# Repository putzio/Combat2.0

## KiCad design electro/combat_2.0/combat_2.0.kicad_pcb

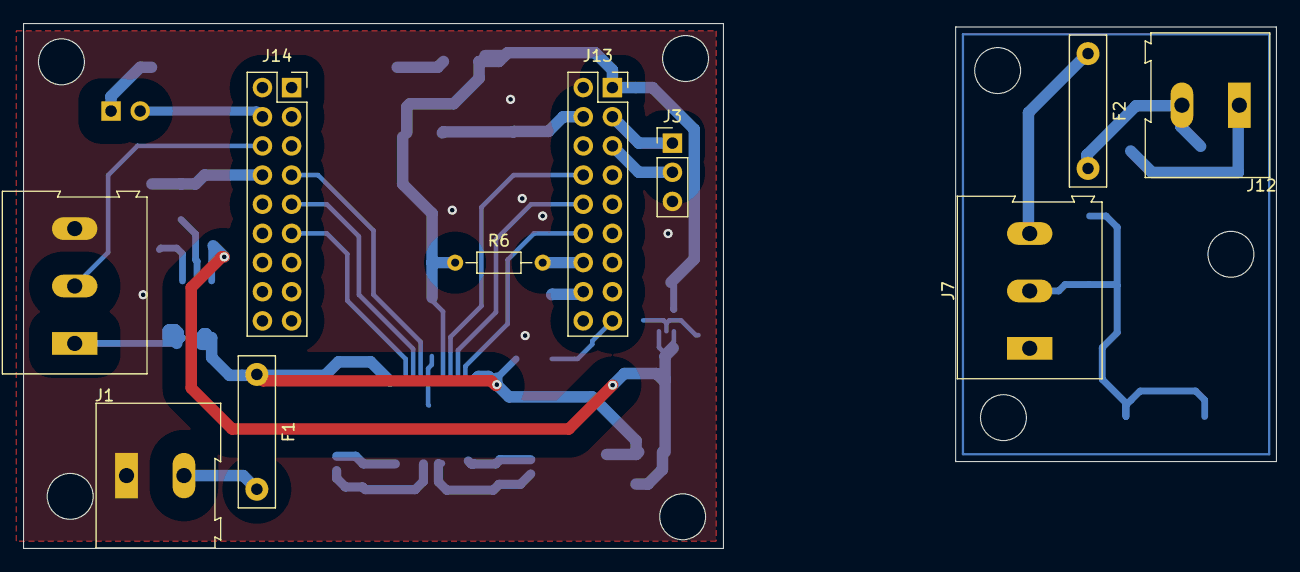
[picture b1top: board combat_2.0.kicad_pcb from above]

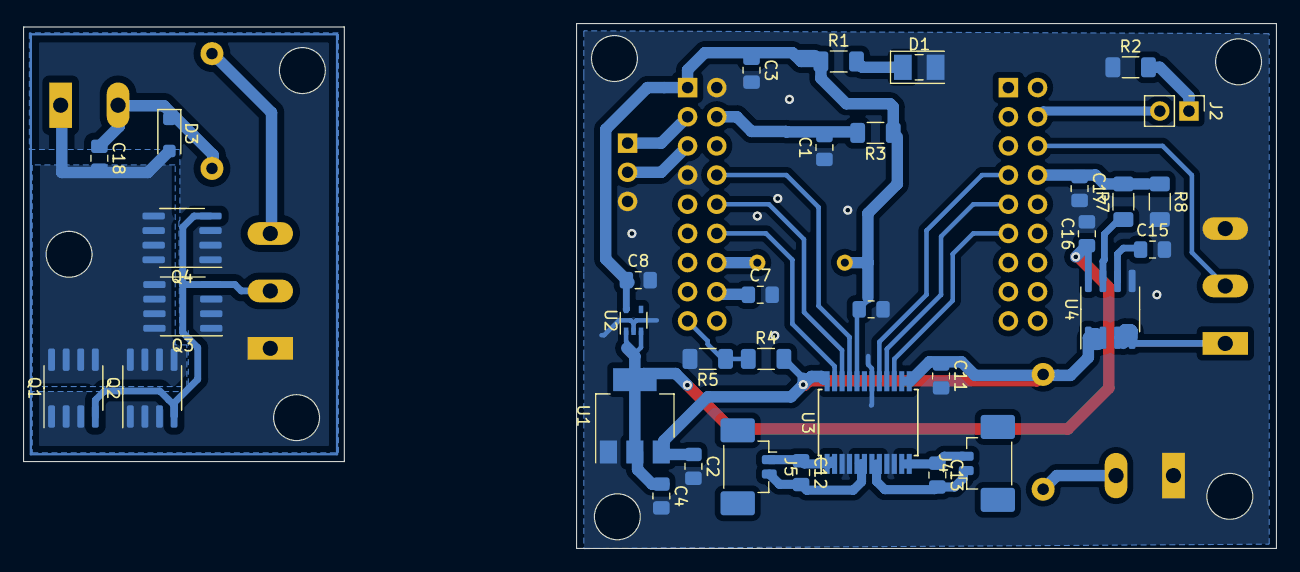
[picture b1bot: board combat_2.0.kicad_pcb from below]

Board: 2 copper layers, 109.1 x 45.7 mm, 44 parts (34 on the bottom side), 31 nets.

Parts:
C1, C7, C12, C13, C16, C18: 0.1uF; C_0805_2012Metric_Pad1.18x1.45mm_HandSolder
C2, C3, C4, C9, C11: 22uF; C_0805_2012Metric_Pad1.18x1.45mm_HandSolder
C8, C17: 1uF; C_0805_2012Metric_Pad1.18x1.45mm_HandSolder
C15: 1nF; C_0805_2012Metric_Pad1.18x1.45mm_HandSolder
D1: PWR; LED_PLCC-2_3x2mm_AK
D3: D; D_SOD-123F
F1: 15A; C_Rect_L13.0mm_W3.0mm_P10.00mm_FKS3_FKP3_MKS4
F2: 12A; C_Rect_L13.0mm_W3.0mm_P10.00mm_FKS3_FKP3_MKS4
J1: BATT; TerminalBlock_Altech_AK300-2_P5.00mm
J2: Conn_01x02_Socket; PinHeader_1x02_P2.54mm_Vertical
J3: UART; PinHeader_1x03_P2.54mm_Vertical
J4, J5: Conn_01x03_Pin; Molex_PicoBlade_53398-0271_1x02-1MP_P1.25mm_Vertical
J6, J7: Conn_01x03_Socket; TerminalBlock_Altech_AK300-3_P5.00mm
J12: MOT_WPN; TerminalBlock_Altech_AK300-2_P5.00mm
J13, J14: Conn_02x09_Odd_Even; PinSocket_2x09_P2.54mm_Vertical
Q1, Q2, Q3, Q4: AO4402G; SOIC-8_3.9x4.9mm_P1.27mm
R1: R; R_1206_3216Metric_Pad1.30x1.75mm_HandSolder
R2: 220; R_1206_3216Metric_Pad1.30x1.75mm_HandSolder
R3: 10kR; R_1206_3216Metric_Pad1.30x1.75mm_HandSolder
R4: 8k2R; R_1206_3216Metric_Pad1.30x1.75mm_HandSolder
R5, R8: 4k7R; R_1206_3216Metric_Pad1.30x1.75mm_HandSolder
R6: 220; R_Axial_DIN0204_L3.6mm_D1.6mm_P7.62mm_Horizontal
R7: 2k7R; R_1206_3216Metric_Pad1.30x1.75mm_HandSolder
U1: AZ1117CH-5.0TRG1; SOT-223-3_TabPin2
U2: LD29150DT33R; SOT-353_SC-70-5
U3: TB6612FNG; SSOP-24_5.3x8.2mm_P0.65mm
U4: ACS712xLCTR-20A; SOIC-8_3.9x4.9mm_P1.27mm

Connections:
+3V3: C3.1, C8.1, C9.1, J13.1, R1.1, R3.1, R6.1, U2.5 (VOUT), U3.20 (VCC)
+5V: C4.1, C16.1, U1.2 (VO), U2.1 (VIN), U2.3 (EN), U4.8 (VCC)
+8V: C2.1, C11.1, F1.1, R4.2, U1.3 (VI), U3.13 (VM2), U3.14 (VM3), U3.24 (VM1), U4.1 (IP+), U4.2 (IP+)
/BAT_LVL_ADC: J13.17, R4.1, R5.1
/DIR_A_1: J13.8, U3.21 (AIN1)
/DIR_A_2: J13.10, U3.22 (AIN2)
/DIR_B_1: J14.7, U3.17 (BIN1)
/DIR_B_2: J14.9, U3.16 (BIN2)
/ESP32 PCB adapter/EN: C1.2, J13.4, R3.2
/ESP32 PCB adapter/IO0: C7.1, J13.16
/ESP32 PCB adapter/IO16: J13.14, R6.2
/ESP32 PCB adapter/IO35: J2.2, J14.4
/MOTOR_CURRENT_ADC: C17.1, J14.8, R7.2, R8.1
/PWM_CH_A: J13.12, U3.23 (PWMA)
/PWM_CH_B: J14.11, U3.15 (PWMB)
/PWM_WEAPON: J6.2, J7.2, J14.6, Q1.4 (G), Q2.4 (G), Q3.4 (G), Q4.4 (G)
/UART_RX: J3.2, J13.5
/UART_TX: J3.1, J13.3
/weapon_motor/MOSFETS_DRAIN: C18.2, D3.2 (A), J12.1, Q1.5 (D_1), Q1.6 (D_2), Q1.7 (D_3), Q1.8 (D_4), Q2.5 (D_1), Q2.6 (D_2), Q2.7 (D_3), Q2.8 (D_4), Q3.5 (D_1), Q3.6 (D_2), Q3.7 (D_3), Q3.8 (D_4), Q4.5 (D_1), Q4.6 (D_2), Q4.7 (D_3), Q4.8 (D_4)
/weapon_motor/MOTOR_IN: C18.1, D3.1 (K), F2.2, J12.2
/weapon_motor/MOTOR_PWR: F2.1, J6.1, J7.3, U4.3 (IP-), U4.4 (IP-)
GND: C1.1, C2.2, C3.2, C4.2, C7.2, C8.2, C9.2, C11.2, C15.2, C16.2, C17.2, D1.1 (K), J1.1, J3.3, J6.3, J7.1, J13.2, J13.7, Q1.1 (S_1), Q1.2 (S_2), Q1.3 (S_3), Q2.1 (S_1), Q2.2 (S_2), Q2.3 (S_3), Q3.1 (S_1), Q3.2 (S_2), Q3.3 (S_3), Q4.1 (S_1), Q4.2 (S_2), Q4.3 (S_3), R2.1, R5.2, R8.2, U1.1 (ADJ), U2.2 (GND), U3.3 (PGND1), U3.4 (PGND1), U3.9 (PGND2), U3.10 (PGND2), U3.18 (GND), U4.5 (GND)
unnamed: D1.2 (A), R1.2
unnamed: F1.2, J1.2
unnamed: J2.1, R2.2
unnamed: C13.2, J4.1, U3.7 (BO2), U3.8 (BO2)
unnamed: C13.1, J4.2, U3.11 (BO1), U3.12 (BO1)
unnamed: C12.1, J5.1, U3.1 (AO1), U3.2 (AO1)
unnamed: C12.2, J5.2, U3.5 (AO2), U3.6 (AO2)
unnamed: C15.1, U4.6 (FILTER)
unnamed: R7.1, U4.7 (VIOUT)

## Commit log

2023-03-17 Electronical schematic
2023-03-17 git submodule with esp node library
2023-03-18 20A Current sensor
2023-03-20 PCB V0
2023-03-20 LDO connection fix
2023-03-23 Added UART connector and voltage divider for battery volt. measurement
2023-03-23 Standarized schematic labels
2023-03-24 Changed resistors to SMD1206 type, hand-soldered version (slightly bigger pads)
2023-03-25 Changed MCU to ESP32-DEVKITC, cleared some ERC errors
2023-03-26 Updated some footprints
2023-03-30 Changed Devkit for ESP32-WROOM device. Added LDO, some other peripherals
2023-03-30 change connectors
2023-04-02 competition rules
2023-04-10 almost ready pcb
2023-04-12 Changed pads to ARKs (connecting two boards together), prepared for etching
2023-04-12 small improvements
2023-04-12 Change in mosfets routing
2023-04-13 Code init, small simple webserver working
2023-04-15 Simple web server working
2023-04-19 updated .gitignore
2023-04-20 Moved functions from main to separate files
2023-04-20 html update
2023-04-20 pinout
2023-04-20 pinout update
2023-04-20 cmbt_pwm driver
2023-04-20 cmbt_motor_driver
2023-04-20 webserver and pinout update
2023-04-20 controlling tasks with pwm and motor tested
